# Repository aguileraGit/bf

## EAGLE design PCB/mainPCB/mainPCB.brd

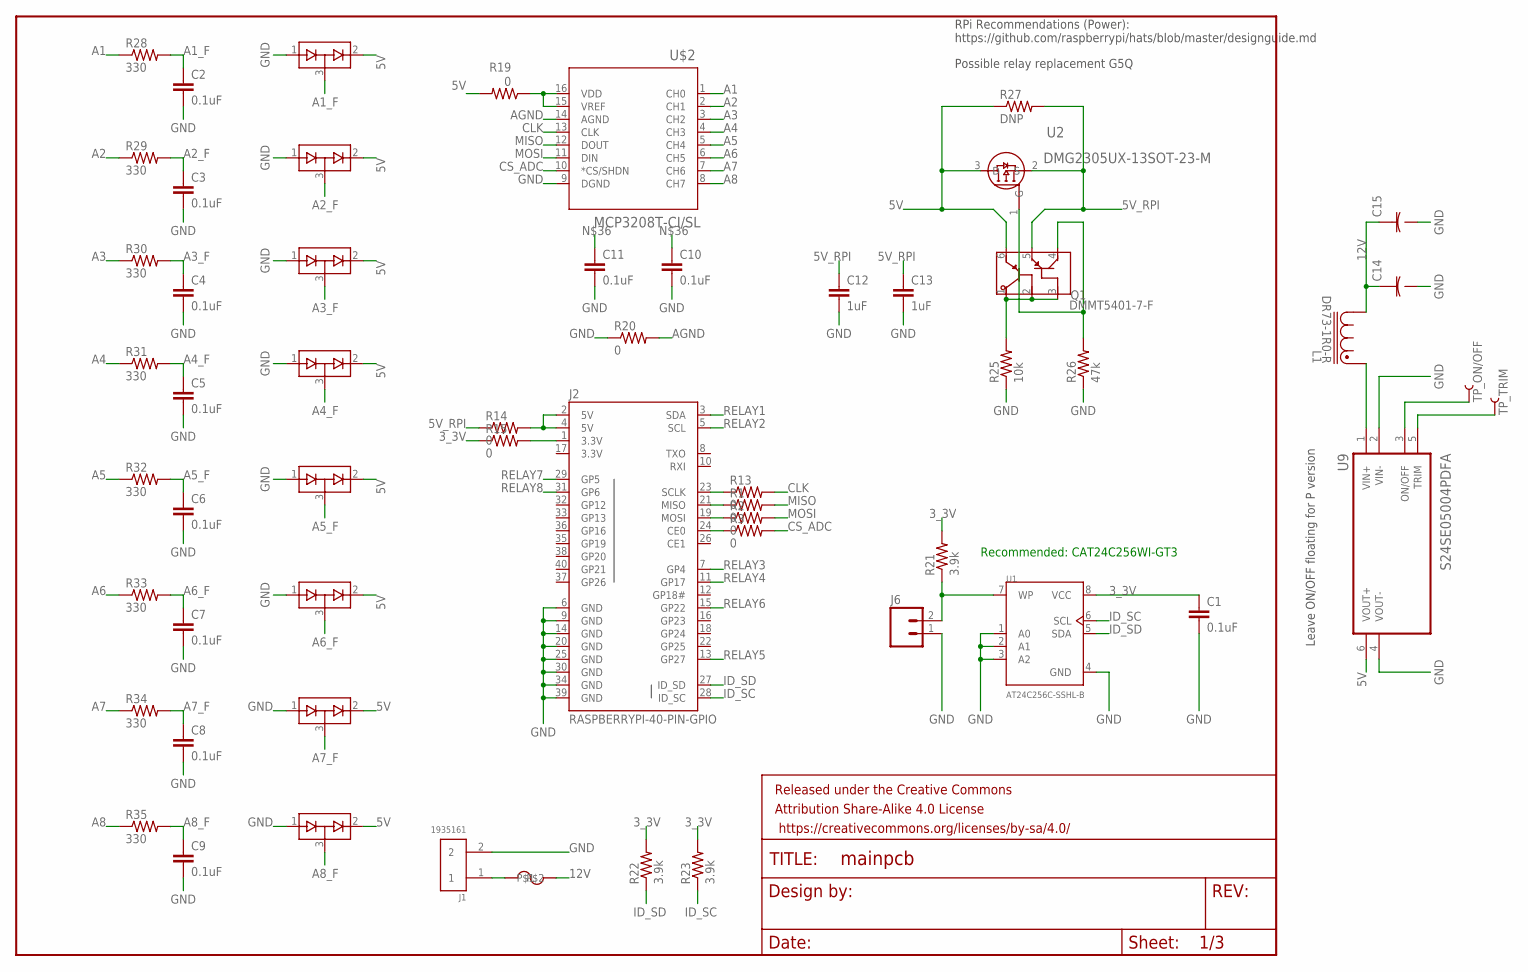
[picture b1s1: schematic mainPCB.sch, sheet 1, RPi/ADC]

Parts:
C1, C2, C3, C4, C5, C6, C7, C8, C9, C10, C11: 0.1uF; 0603-CAP
C12, C13: 1uF; 1206-CAP
C14, C15: EEE-HA1C471UPCAP_PAN_EEE_F-L; CAP_PAN_EEE_F-L
D1, D5, D7, D12, D13, D14, D15, D16: BAV99-7-F; SOT23-3
F9: 3544-2
FRAME2: FRAME-LETTERNO_PACKAGE; DUMMY
J1: 1935161; PHOENIX_1935161
J2: RASPBERRYPI-40-PIN-GPIO; 2X20-SHROUDED
J6: M02PTH; 1X02
L1: DR73-1R0-R; DR73
Q1: DMMT5401-7-F; SOT26
R1, R2, R3, R13, R19, R20: 0; 0603-RES
R14, R15: 0; 1206
R21, R22, R23: 3.9k; 0603-RES
R25: 10k; 0603-RES
R26: 47k; 0603-RES
R27: DNP; 1206
R28, R29, R30, R31, R32, R33, R34, R35: 330; 0603-RES
TP_ON/OFF: TEST-POINT3X5; PAD.03X.05
TP_TRIM: TEST-POINT3X5; PAD.03X.05
U1: AT24C256C-SSHL-B; SOIC127P600X175-8N
U2: DMG2305UX-13SOT-23-M; SOT-23-M
U9: S24SE05004PDFA; CONV_S24SE05002PDFA
U$2: MCP3208T-CI/SL; SOIC16-N_MC

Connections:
3.3V: J2.17 (3.3V)
3_3V: C1.1, R15.1, R21.2, R22.2, R23.2, U1.8 (VCC)
5V: D1.2 (C2), D5.2 (C2), D7.2 (C2), D12.2 (C2), D13.2 (C2), D14.2 (C2), D15.2 (C2), D16.2 (C2), Q1.6 (E1), R19.2, R27.1, U2.3 (D), U9.6 (VOUT+); also elsewhere on the board
5V_RPI: C12.1, C13.1, Q1.5 (E2), R14.1, R27.2, U2.2 (S)
12V: C14.1 (11), C15.1 (11), F9.P$3, F9.P$4, L1.2; also elsewhere on the board
A1: R28.1, U$2.1 (CH0)
A1_F: C2.1, D1.3 (COM), R28.2; also elsewhere on the board
A2: R29.1, U$2.2 (CH1)
A2_F: C3.1, D5.3 (COM), R29.2; also elsewhere on the board
A3: R30.1, U$2.3 (CH2)
A3_F: C4.1, D7.3 (COM), R30.2; also elsewhere on the board
A4: R31.1, U$2.4 (CH3)
A4_F: C5.1, D12.3 (COM), R31.2; also elsewhere on the board
A5: R32.1, U$2.5 (CH4)
A5_F: C6.1, D13.3 (COM), R32.2; also elsewhere on the board
A6: R33.1, U$2.6 (CH5)
A6_F: C7.1, D14.3 (COM), R33.2; also elsewhere on the board
A7: R34.1, U$2.7 (CH6)
A7_F: C8.1, D15.3 (COM), R34.2; also elsewhere on the board
A8: R35.1, U$2.8 (CH7)
A8_F: C9.1, D16.3 (COM), R35.2; also elsewhere on the board
AGND: R20.2, U$2.14 (AGND)
CLK: R13.2, U$2.13 (CLK)
CS_ADC: R3.2, U$2.10 (*CS/SHDN)
GND: C1.2, C2.2, C3.2, C4.2, C5.2, C6.2, C7.2, C8.2, C9.2, C10.2, C11.2, C12.2, C13.2, C14.2 (22), C15.2 (22), D1.1 (A1), D5.1 (A1), D7.1 (A1), D12.1 (A1), D13.1 (A1), D14.1 (A1), D15.1 (A1), D16.1 (A1), J1.2, J2.6 (GND), J2.9 (GND), J2.14 (GND), J2.20 (GND), J2.25 (GND), J2.30 (GND), J2.34 (GND), J2.39 (GND), J6.1, R20.1, R25.1, R26.1, U1.1 (A0), U1.2 (A1), U1.3 (A2), U1.4 (GND), U9.2 (VIN-), U9.4 (VOUT-), U$2.9 (DGND); also elsewhere on the board
ID_SC: J2.28 (ID_SC), R23.1, U1.6 (SCL)
ID_SD: J2.27 (ID_SD), R22.1, U1.5 (SDA)
MISO: R1.2, U$2.12 (DOUT)
MOSI: R2.2, U$2.11 (DIN)
unnamed: J2.2 (5V), J2.4 (5V), R14.2
unnamed: J2.1 (3.3V), R15.2
unnamed: J2.23 (SCLK), R13.1
unnamed: J2.21 (MISO), R1.1
unnamed: J2.19 (MOSI), R2.1
unnamed: J2.24 (CE0), R3.1
unnamed: Q1.1 (C1), Q1.2 (B1), Q1.3 (B2), R25.2
unnamed: Q1.4 (C2), R26.2, U2.1 (G)
unnamed: TP_ON/OFF.P$1, U9.3 (ON/OFF)
unnamed: C10.1, C11.1, R19.1, U$2.15 (VREF), U$2.16 (VDD)
unnamed: L1.1, U9.1 (VIN+)
unnamed: TP_TRIM.P$1, U9.5 (TRIM)
unnamed: F9.P$1, F9.P$2, J1.1
RELAY1: J2.3 (SDA); also elsewhere on the board
RELAY2: J2.5 (SCL); also elsewhere on the board
RELAY3: J2.7 (GP4); also elsewhere on the board
RELAY4: J2.11 (GP17); also elsewhere on the board
RELAY5: J2.13 (GP27); also elsewhere on the board
RELAY6: J2.15 (GP22); also elsewhere on the board
RELAY7: J2.29 (GP5); also elsewhere on the board
RELAY8: J2.31 (GP6); also elsewhere on the board
WP: J6.2, R21.1, U1.7 (WP)

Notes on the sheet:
Recommended: CAT24C256WI-GT3
RPi Recommendations (Power): https://github.com/raspberrypi/hats/blob/master/designguide.md
Possible relay replacement G5Q
Leave ON/OFF floating for P version

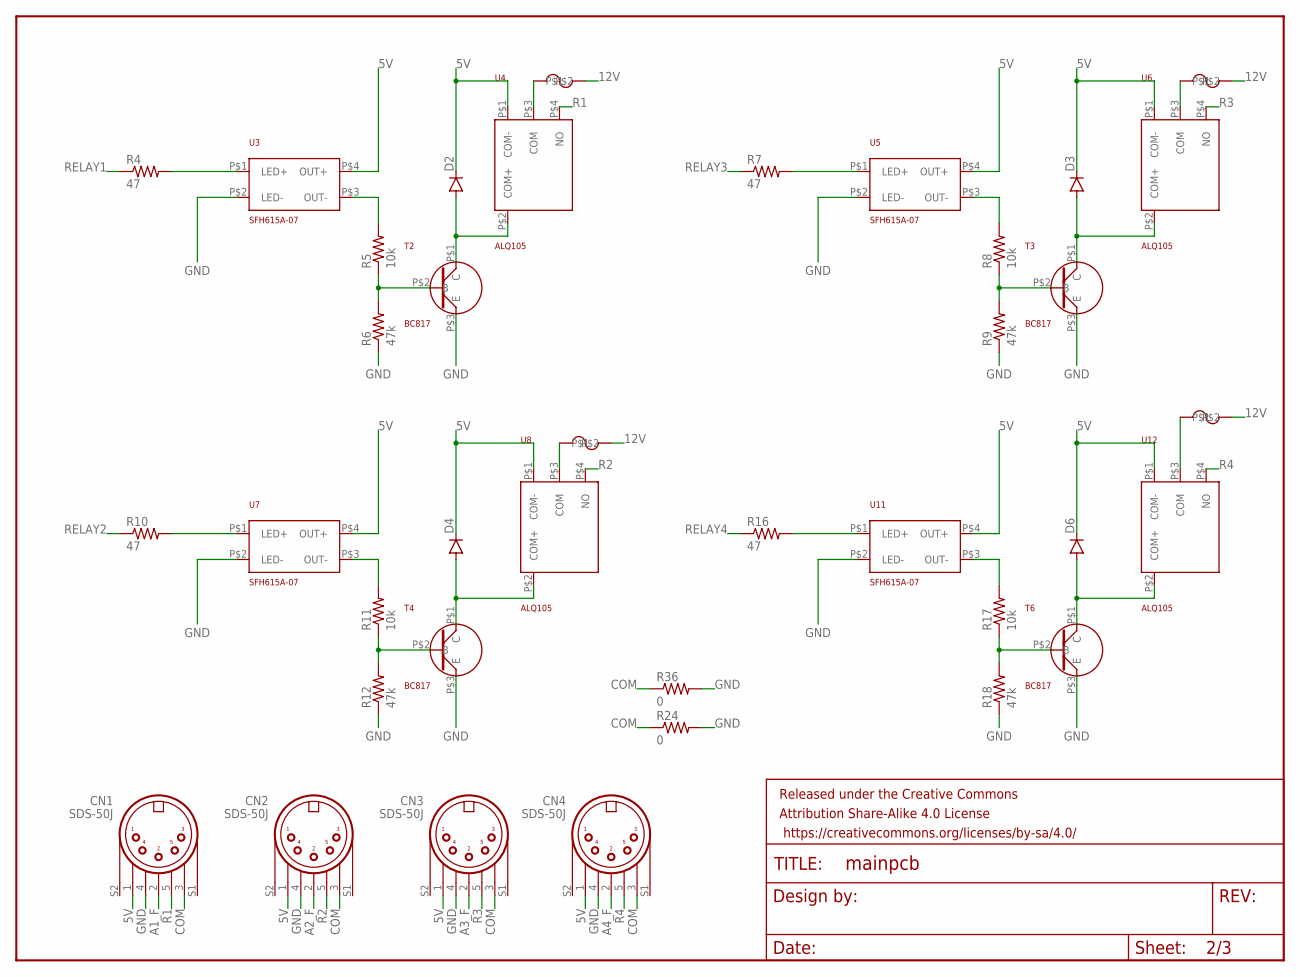
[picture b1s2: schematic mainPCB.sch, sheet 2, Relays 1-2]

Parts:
CN1, CN2, CN3, CN4: SDS-50J
D2, D3, D4, D6: DIODESMA; SMA-DIODE
F1, F2, F3, F4: 3544-2
FRAME1: FRAME-LETTERNO_PACKAGE; DUMMY
R4, R7, R10, R16: 47; 0603-RES
R5, R8, R11, R17: 10k; 0603-RES
R6, R9, R12, R18: 47k; 0603-RES
R24, R36: 0; 1206
T2, T3, T4, T6: BC817
U3, U5, U7, U11: SFH615A-07
U4, U6, U8, U12: ALQ105

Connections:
5V: CN1.1, CN2.1, CN3.1, CN4.1, D2.C, D3.C, D4.C, D6.C, U3.P$4 (OUT+), U4.P$1 (COM-), U5.P$4 (OUT+), U6.P$1 (COM-), U7.P$4 (OUT+), U8.P$1 (COM-), U11.P$4 (OUT+), U12.P$1 (COM-); also elsewhere on the board
12V: F1.P$3, F1.P$4, F2.P$3, F2.P$4, F3.P$3, F3.P$4, F4.P$3, F4.P$4; also elsewhere on the board
A1_F: CN1.2; also elsewhere on the board
A2_F: CN2.2; also elsewhere on the board
A3_F: CN3.2; also elsewhere on the board
A4_F: CN4.2; also elsewhere on the board
COM: CN1.3, CN2.3, CN3.3, CN4.3, R24.1, R36.1; also elsewhere on the board
GND: CN1.4, CN2.4, CN3.4, CN4.4, R6.1, R9.1, R12.1, R18.1, R24.2, R36.2, T2.P$3 (E), T3.P$3 (E), T4.P$3 (E), T6.P$3 (E), U3.P$2 (LED-), U5.P$2 (LED-), U7.P$2 (LED-), U11.P$2 (LED-); also elsewhere on the board
unnamed: F1.P$1, F1.P$2, U4.P$3 (COM)
unnamed: F2.P$1, F2.P$2, U8.P$3 (COM)
unnamed: F4.P$1, F4.P$2, U12.P$3 (COM)
unnamed: F3.P$1, F3.P$2, U6.P$3 (COM)
unnamed: R4.2, U3.P$1 (LED+)
unnamed: R5.2, U3.P$3 (OUT-)
unnamed: R5.1, R6.2, T2.P$2 (B)
unnamed: D2.A, T2.P$1 (C), U4.P$2 (COM+)
unnamed: R7.2, U5.P$1 (LED+)
unnamed: R8.2, U5.P$3 (OUT-)
unnamed: R8.1, R9.2, T3.P$2 (B)
unnamed: D3.A, T3.P$1 (C), U6.P$2 (COM+)
unnamed: R10.2, U7.P$1 (LED+)
unnamed: R11.2, U7.P$3 (OUT-)
unnamed: R11.1, R12.2, T4.P$2 (B)
unnamed: D4.A, T4.P$1 (C), U8.P$2 (COM+)
unnamed: R16.2, U11.P$1 (LED+)
unnamed: R17.2, U11.P$3 (OUT-)
unnamed: R17.1, R18.2, T6.P$2 (B)
unnamed: D6.A, T6.P$1 (C), U12.P$2 (COM+)
R1: CN1.5, U4.P$4 (NO)
R2: CN2.5, U8.P$4 (NO)
R3: CN3.5, U6.P$4 (NO)
R4: CN4.5, U12.P$4 (NO)
RELAY1: R4.1; also elsewhere on the board
RELAY2: R10.1; also elsewhere on the board
RELAY3: R7.1; also elsewhere on the board
RELAY4: R16.1; also elsewhere on the board

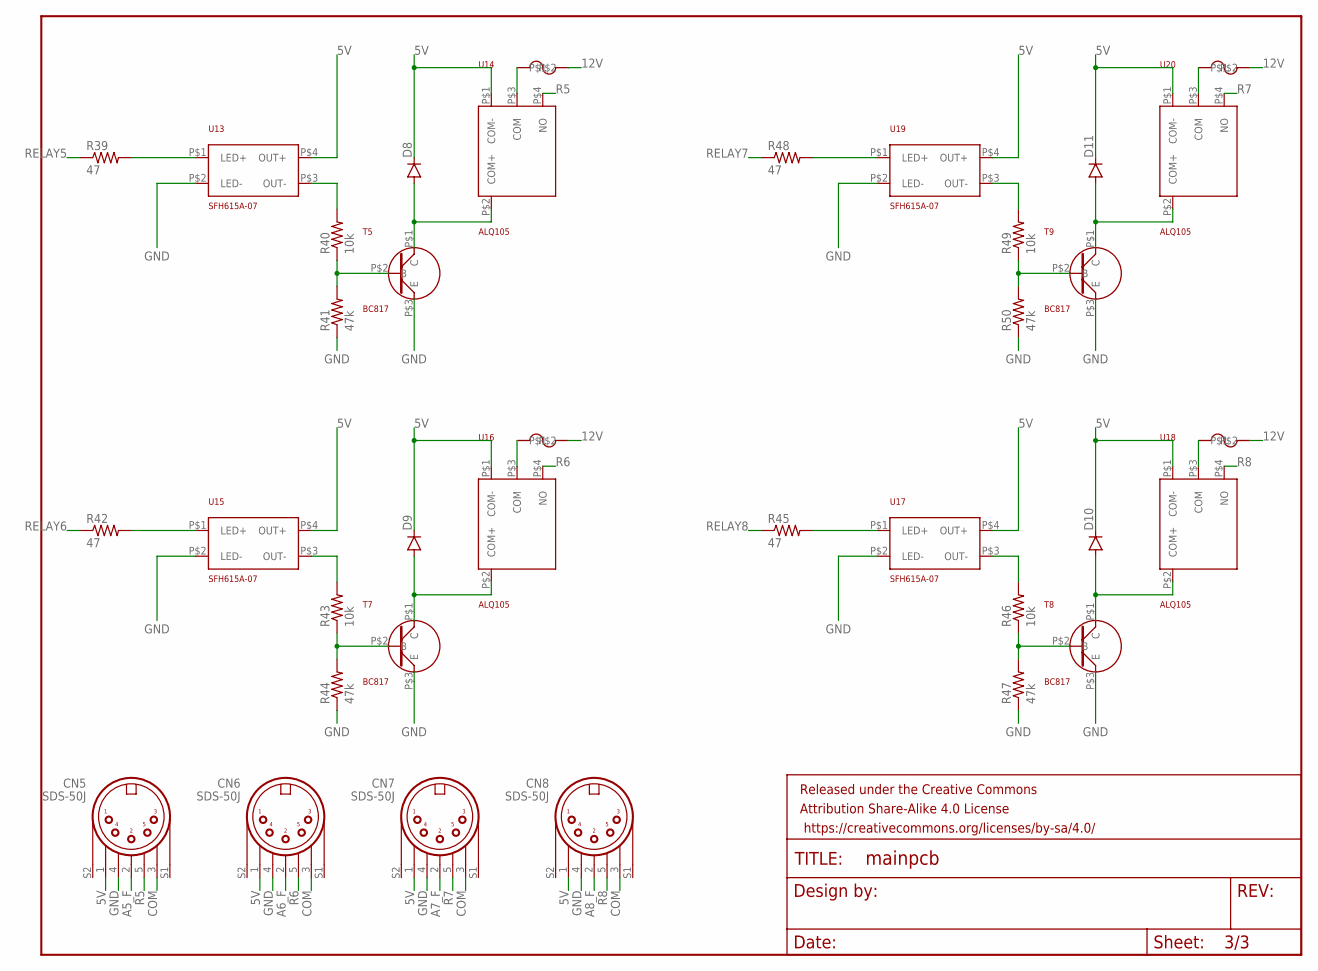
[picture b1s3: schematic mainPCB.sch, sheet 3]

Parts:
CN5, CN6, CN7, CN8: SDS-50J
D8, D9, D10, D11: DIODESMA; SMA-DIODE
F5, F6, F7, F8: 3544-2
FRAME3: FRAME-LETTER; CREATIVE_COMMONS
R39, R42, R45, R48: 47; 0603-RES
R40, R43, R46, R49: 10k; 0603-RES
R41, R44, R47, R50: 47k; 0603-RES
T5, T7, T8, T9: BC817
U13, U15, U17, U19: SFH615A-07
U14, U16, U18, U20: ALQ105

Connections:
5V: CN5.1, CN6.1, CN7.1, CN8.1, D8.C, D9.C, D10.C, D11.C, U13.P$4 (OUT+), U14.P$1 (COM-), U15.P$4 (OUT+), U16.P$1 (COM-), U17.P$4 (OUT+), U18.P$1 (COM-), U19.P$4 (OUT+), U20.P$1 (COM-); also elsewhere on the board
12V: F5.P$3, F5.P$4, F6.P$3, F6.P$4, F7.P$3, F7.P$4, F8.P$3, F8.P$4; also elsewhere on the board
A5_F: CN5.2; also elsewhere on the board
A6_F: CN6.2; also elsewhere on the board
A7_F: CN7.2; also elsewhere on the board
A8_F: CN8.2; also elsewhere on the board
COM: CN5.3, CN6.3, CN7.3, CN8.3; also elsewhere on the board
GND: CN5.4, CN6.4, CN7.4, CN8.4, R41.1, R44.1, R47.1, R50.1, T5.P$3 (E), T7.P$3 (E), T8.P$3 (E), T9.P$3 (E), U13.P$2 (LED-), U15.P$2 (LED-), U17.P$2 (LED-), U19.P$2 (LED-); also elsewhere on the board
unnamed: F5.P$1, F5.P$2, U14.P$3 (COM)
unnamed: F6.P$1, F6.P$2, U16.P$3 (COM)
unnamed: F7.P$1, F7.P$2, U20.P$3 (COM)
unnamed: F8.P$1, F8.P$2, U18.P$3 (COM)
unnamed: R39.2, U13.P$1 (LED+)
unnamed: R40.2, U13.P$3 (OUT-)
unnamed: R40.1, R41.2, T5.P$2 (B)
unnamed: D8.A, T5.P$1 (C), U14.P$2 (COM+)
unnamed: R42.2, U15.P$1 (LED+)
unnamed: R43.2, U15.P$3 (OUT-)
unnamed: R43.1, R44.2, T7.P$2 (B)
unnamed: D9.A, T7.P$1 (C), U16.P$2 (COM+)
unnamed: R45.2, U17.P$1 (LED+)
unnamed: R46.2, U17.P$3 (OUT-)
unnamed: R46.1, R47.2, T8.P$2 (B)
unnamed: D10.A, T8.P$1 (C), U18.P$2 (COM+)
unnamed: R48.2, U19.P$1 (LED+)
unnamed: R49.2, U19.P$3 (OUT-)
unnamed: R49.1, R50.2, T9.P$2 (B)
unnamed: D11.A, T9.P$1 (C), U20.P$2 (COM+)
R5: CN5.5, U14.P$4 (NO)
R6: CN6.5, U16.P$4 (NO)
R7: CN7.5, U20.P$4 (NO)
R8: CN8.5, U18.P$4 (NO)
RELAY5: R39.1; also elsewhere on the board
RELAY6: R42.1; also elsewhere on the board
RELAY7: R48.1; also elsewhere on the board
RELAY8: R45.1; also elsewhere on the board

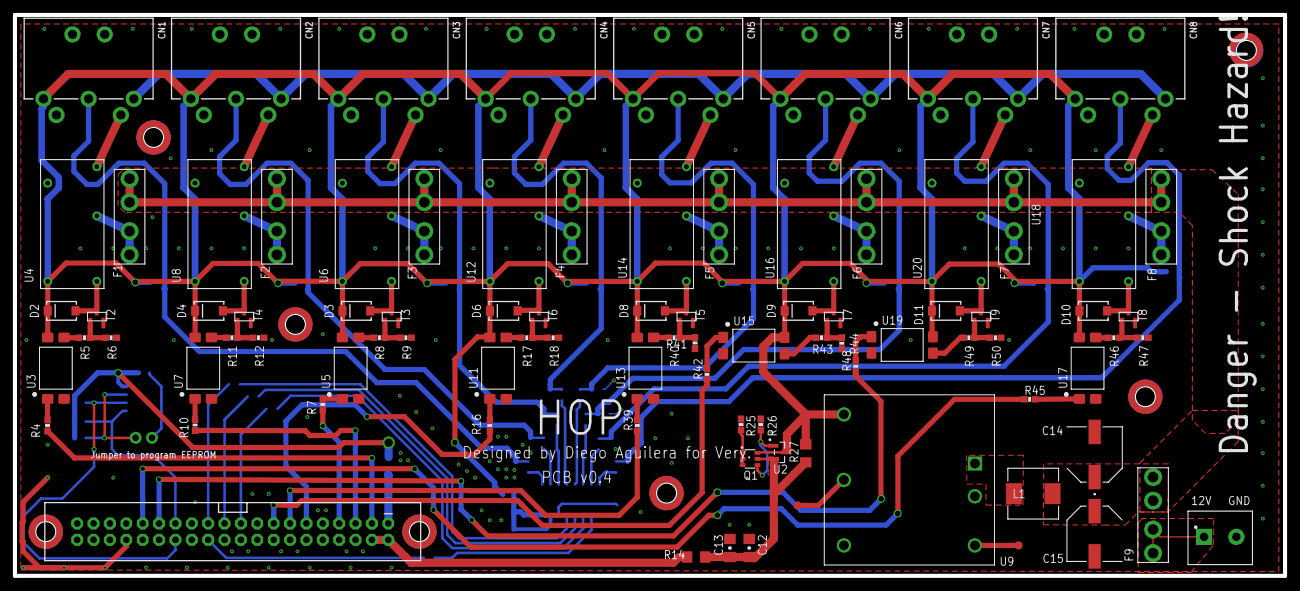
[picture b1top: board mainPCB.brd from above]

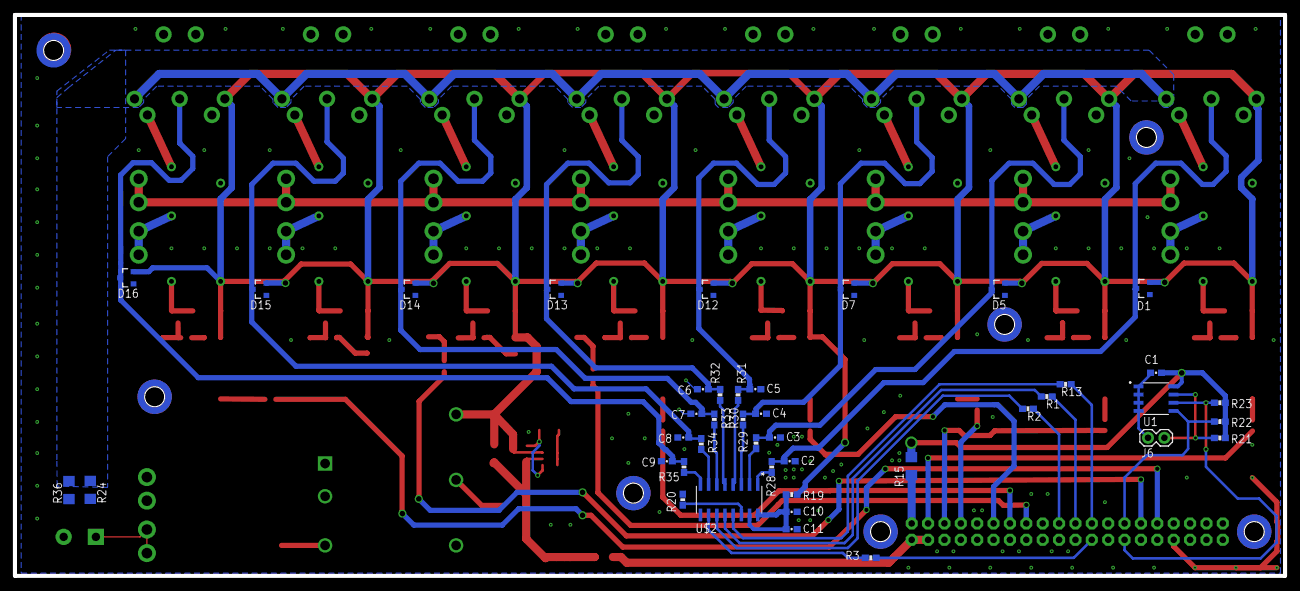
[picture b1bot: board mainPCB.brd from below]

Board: 2 copper layers, 197.0 x 87.0 mm, 134 parts (42 on the bottom side), 99 nets.

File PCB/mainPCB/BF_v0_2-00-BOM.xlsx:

Populate | Qty | Value | Device | Package | Parts | Manufacture PN | DigiKey PN | 1 |  | 10 |  | 100 |  | Description | AVAILABILITY | DESCRIPTION | DESIGNER | DIGI-KEY_PART_NUMBER | DIGI-KEY_PURCHASE_URL | MANUFACTURER_PART_NUMBER | MF | MP | PACKAGE | PRICE | PROD_ID | VALUE | VENDOR | VERSION
Y | 9 |  | DIODESMA | SMA-DIODE | D2, D3, D4, D5, D6, D8, D9, D10, D11 | CDBA5200-HF | 641-1706-1-ND | 0.59 | 5.31 | 0.49299999999999999 | 44.37 | 0.36990000000000001 | 332.91 | Diode
Y | 1 |  | M02PTH | 1X02 | J6 | M20-9990246 | 952-2262-ND | 0.11 | 0.11 | 9.9000000000000005E-2 | 0.99 | 6.0900000000000003E-2 | 6.09 | Standard 2-pin 0.1 header. Use with"
Y | 6 | 0 | RESISTOR0603-RES | 0603-RES | R1, R2, R3, R13, R19, R20 | RC0603JR-070RL | 311-0.0GRCT-ND | 0.1 | 0.60000000000000009 | 0.01 | 0.6 | 4.1000000000000003E-3 | 2.4600000000000004 | Resistor
Y | 3 | 0 | RESISTOR1206 | 1206 | R14, R15, R24 | RC1206JR-070RL | 311-0.0ERCT-ND | 0.1 | 0.30000000000000004 | 2.4E-2 | 0.72 | 9.7000000000000003E-3 | 2.91 | Resistor
Y | 11 | 0.1uF | 0.1UF-25V(+80/-20%)(0603) | 0603-CAP | C1, C2, C3, C4, C5, C6, C7, C8, C9, C10, C11 | GRM188R70J104KA01D | 490-9730-1-ND | 0.1 | 1.1000000000000001 | 7.0999999999999994E-2 | 7.81 | 3.1600000000000003E-2 | 34.760000000000005 | CAP-00810 |  |  |  |  |  |  |  |  |  |  | CAP-00810 | 0.1uF
Y | 2 | 10uF | 1.0UF50V10%(1206) | 1206-CAP | C12, C13 | LMK316B7106KL-TD | 587-2596-1-ND | 0.27 | 0.54 | 0.182 | 3.6399999999999997 | 0.1032 | 20.64 | CAP-09822 |  |  |  |  |  |  |  |  |  |  | CAP-09822 | 1.0uF
Y | 9 | 10k | RESISTOR0603-RES | 0603-RES | R5, R8, R11, R17, R25, R40, R43, R46, R49 | RC0603FR-0710KL | 311-10.0KHRCT-ND | 0.1 | 0.9 | 1.4999999999999999E-2 | 1.3499999999999999 | 6.0000000000000001E-3 | 5.4 | Resistor
Y | 1 | 1776244-4 | 1776244-4 | 1776244-4 | CON1 | 1776244-4 | A97998-ND | 1.74 | 1.74 | 1.2250000000000001 | 12.25 | 1.0319 | 103.19 | TE 1776244-4
Y | 3 | 3.9k | RESISTOR0603-RES | 0603-RES | R21, R22, R23 | RC0603FR-073K9L | 311-3.90KHRDKR-ND | 0.1 | 0.30000000000000004 | 1.4999999999999999E-2 | 0.44999999999999996 | 6.0000000000000001E-3 | 1.8 | Resistor
Y | 8 | 330 | RESISTOR0603-RES | 0603-RES | R28, R29, R30, R31, R32, R33, R34, R35 | RC0603FR-07300RL | 311-300HRCT-ND | 0.1 | 0.8 | 1.4999999999999999E-2 | 1.2 | 6.0000000000000001E-3 | 4.8 | Resistor
Y | 8 | 3544-2 | 3544-2 | 3544-2 | F1, F2, F3, F4, F5, F6, F7, F8 | 3544-2 | 36-3544-2-ND | 0.91 | 7.28 | 0.77800000000000002 | 62.24 | 0.6714 | 537.12 | Keystone Electronics Fuse Holder - 3544-2
Y | 8 | 47 | RESISTOR0603-RES | 0603-RES | R4, R7, R10, R16, R39, R42, R45, R48 | RC0603FR-0747RL | 311-47.0HRCT-ND | 0.1 | 0.8 | 1.4999999999999999E-2 | 1.2 | 6.0000000000000001E-3 | 4.8 | Resistor
Y | 9 | 47k | RESISTOR0603-RES | 0603-RES | R6, R9, R12, R18, R26, R41, R44, R47, R50 | RC0603FR-0747KL | 311-47.0KHRCT-ND | 0.1 | 0.9 | 1.4999999999999999E-2 | 1.3499999999999999 | 6.0000000000000001E-3 | 5.4 | Resistor
Y | 8 | ALQ105 | ALQ105 | ALQ105 | U4, U6, U8, U12, U14, U16, U18, U20 | ALQ105 | 255-3565-ND | 2.42 | 19.36 | 2.2730000000000001 | 181.84 | 1.8180000000000001 | 1454.4 | ALQ105 Solenoid
Y | 1 | AT24C256C-SSHL-B | AT24C256C-SSHL-B | SOIC127P600X175-8N | U1 | AT24C256C-SSHL-B | AT24C256C-SSHL-B-ND | 0.69 | 0.69 | 0.63100000000000001 | 6.3100000000000005 | 0.55369999999999997 | 55.37 | EEPROM Serial-2Wire 256K-bit 32K x 8 1.8V/2.5V/3.3V/5V 8-Pin SOIC Bulk |  | EEPROM Serial-2Wire 256K-bit 32K x 8 1.8V/2.5V/3.3V/5V 8-Pin SOIC Bulk |  | AT24C256C-SSHL-B-ND | https://www.digikey.com/product-detail/en/microchip-technolo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 |  | Atmel | AT24C256C-SSHL-B | SOIC-8 Atmel
Y | 8 | BC817 | BC817 | BC817 | T2, T3, T4, T5, T6, T7, T8, T9 | BC817-25-7-F | BC817-25FDICT-ND | 0.22 | 1.76 | 0.183 | 14.64 | 9.69E-2 | 77.52 | NPN Transistor BC817
Y | 1 | DMG2305UX-13SOT-23-M | DMG2305UX-13SOT-23-M | SOT-23-M | U2 | DMG2305UX-13 | DMG2305UX-13DICT-ND | 0.44 | 0.44 | 0.39800000000000002 | 3.9800000000000004 | 0.2228 | 22.28 |  |  |  |  |  |  | DMG2305UX13 |  |  |  |  |  |  | Diodes Inc
Y | 1 | DMMT5401-7-F | DMMT5401-7-F | SOT26 | Q1 | DMMT5401-7-F | DMMT5401-FDICT-ND | 0.46 | 0.46 | 0.34599999999999997 | 3.46 | 0.21529999999999999 | 21.529999999999998 | http://octopart.com/dmmt5401-7-f-diodes+inc.-39560120 |  | DMMT5401 Series PNP 150 V 300 mW Small Signal Transistor SMT - SOT-26-6 |  | DMMT5401-FDICT-ND | https://www.digikey.com/product-detail/en/diodes-incorporate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 |  | Diodes Inc. | DMMT5401-7-F | SOT-23 Diodes Inc.
N | 1 | DNP | RESISTOR1206 | 1206 | R27 |  |  |  |  |  |  |  |  | Resistor
Y | 2 | EEE-HA1C471UPCAP_PAN_EEE_F-L | EEE-HA1C471UPCAP_PAN_EEE_F-L | CAP_PAN_EEE_F-L | C14, C15 | EEE-HA1C471UP | PCE4192CT-ND | 0.68 | 1.36 | 0.48099999999999998 | 9.6199999999999992 | 0.31659999999999999 | 63.32 |  |  |  |  |  |  | EEEHA1C471UP |  |  |  |  |  |  | PANASONIC
N | 1 | FRAME-LETTER | FRAME-LETTER | CREATIVE_COMMONS | FRAME3 |  |  |  |  |  |  |  |  | Schematic Frame
N | 2 | FRAME-LETTERNO_PACKAGE | FRAME-LETTERNO_PACKAGE | DUMMY | FRAME1, FRAME2 |  |  |  |  |  |  |  |  | Schematic Frame |  |  | Nobody |  |  |  |  |  |  |  |  |  |  | v01
Y | 1 | MCP3208T-CI/SL | MCP3208T-CI/SL | SOIC16-N_MC | U$2 | MCP3208T-CI/SL | MCP3208T-CI/SLCT-ND | 3.65 | 3.65 | 3.65 | 36.5 | 2.7719999999999998 | 277.2 | Microchip MCP3208 ADC | Good | 8 Channel SPI Serial Interface 2.7 V 12-Bit A/D Converter SMT - SOIC-16 |  |  |  |  | Microchip | MCP3208T-CI/SL | SOIC-16 Microchip | 3.04 USD
N | 1 | RASPBERRYPI-40-PIN-GPIO | RASPBERRYPI-40-PIN-GPIO | 2X20-SHROUDED | J2 |  |  |  |  |  |  |  |  | Second Generation Raspberry Pi GPIO Header
Y | 8 | SDS-50J | SDS-50J | SDS-50J | CN1, CN2, CN3, CN4, CN5, CN6, CN7, CN8 | SDS-50J | CP-2350-ND | 1.17 | 9.36 | 1.028 | 82.240000000000009 | 0.88660000000000005 | 709.28000000000009 | DIN 5-Pin - Circular | Good | 5 Pin%2C Right-Angle Receptacle%2C 180%C2%B0 |  |  |  |  | CUI | SDS-50J | None | 0.77 USD
Y | 8 | SFH615A-07 | SFH615A-07 | SFH615A-07 | U3, U5, U7, U11, U13, U15, U17, U19 | SFH615A-4X017T | SFH615A-4X017TCT-ND | 1.03 | 8.24 | 0.84 | 67.2 | 0.58160000000000001 | 465.28000000000003 | Vishay Optocoupler SFH615A-007
N | 1 |  | Fuse |  |  | 0287002.PXCN | F4192-ND | 0.28000000000000003 | 0.28000000000000003 | 0.26 | 2.6 | 0.216 | 21.6
 |  |  |  |  |  |  | Total Cost |  | 66.279999999999987 |  | 546.56000000000006 |  | 4230.0600000000013
 |  |  |  |  |  |  | Cost per board |  | 66.279999999999987 |  | 54.656000000000006 |  | 42.30060000000001

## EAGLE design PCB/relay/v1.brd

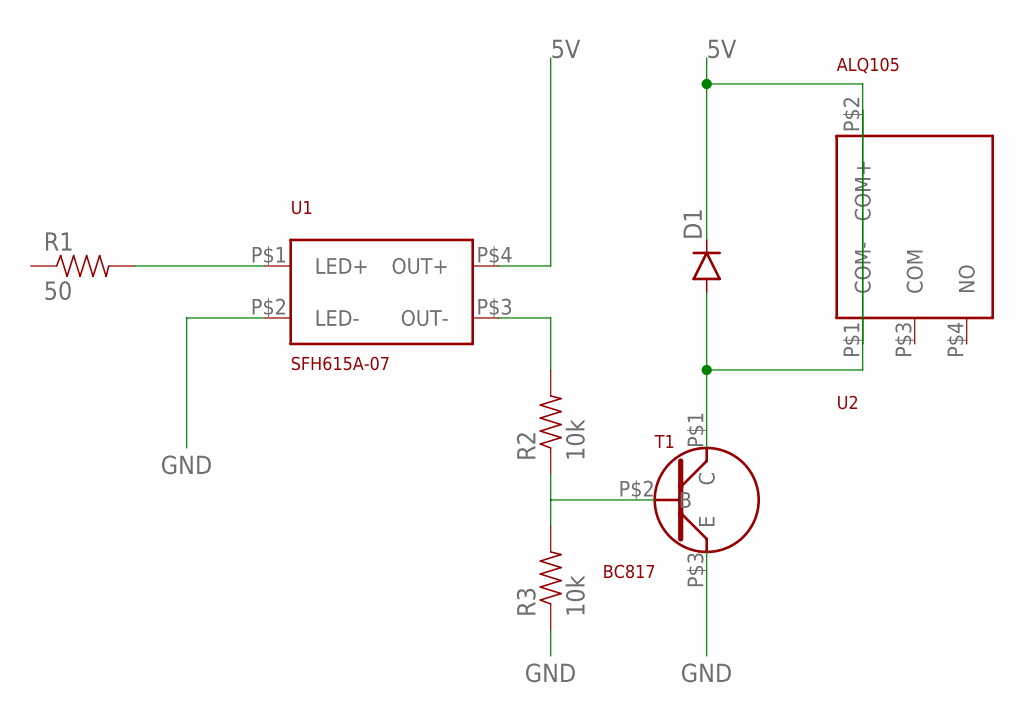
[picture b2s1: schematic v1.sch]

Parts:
D1: DIODESMA; SMA-DIODE
R1: 50; 0603-RES
R2, R3: 10k; 0603-RES
T1: BC817
U1: SFH615A-07
U2: ALQ105

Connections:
5V: D1.C, U1.P$4 (OUT+), U2.P$1 (COM-)
GND: R3.1, T1.P$3 (E), U1.P$2 (LED-)
unnamed: R1.2, U1.P$1 (LED+)
unnamed: R2.2, U1.P$3 (OUT-)
unnamed: R2.1, R3.2, T1.P$2 (B)
unnamed: D1.A, T1.P$1 (C), U2.P$2 (COM+)

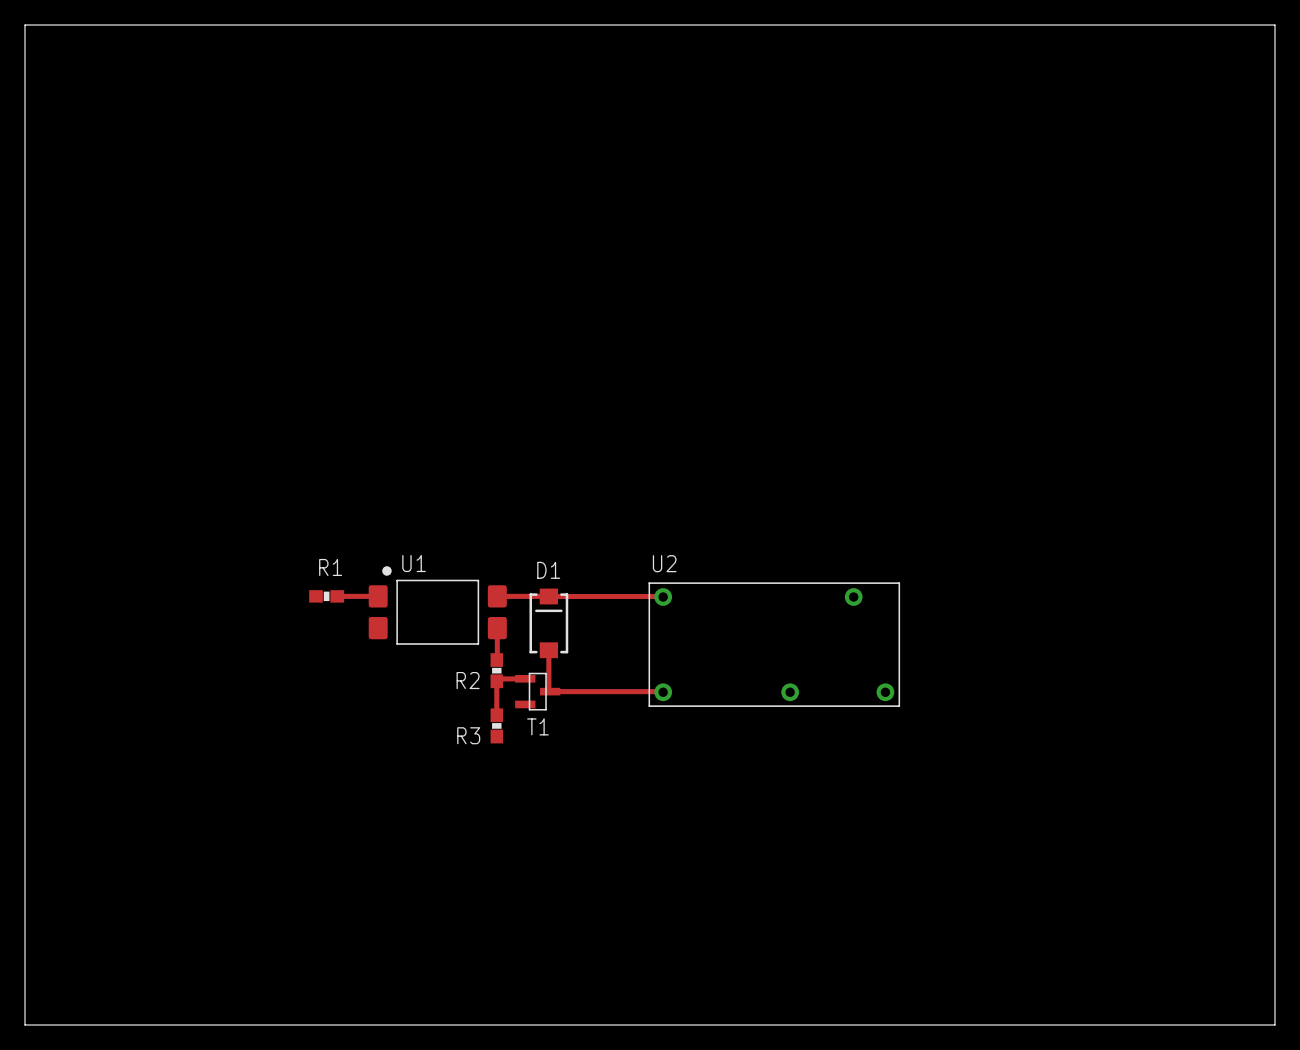
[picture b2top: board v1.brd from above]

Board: 2 copper layers, 100.0 x 80.0 mm, 7 parts (0 on the bottom side), 6 nets.

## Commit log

2017-10-07 Version 1 Ordered.
2017-12-04 Adding files for v0.2
2017-12-10 Removed Diode.
2018-01-02 Adding files
2018-02-24 Technically version 0.4. Sending it to JLCPCB for production.
2018-03-08 Added all design files for v0.4. Cleaned up old files.
2018-03-08 Adding Design Files for v0.4

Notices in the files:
parts and their libraries:
SparkFun-DiscreteSemi: Licensing: Creative Commons ShareAlike 4.0 International - https://creativecommons.org/licenses/by-sa/4.0
SparkFun-Aesthetics: Released under the Creative Commons
SparkFun-Aesthetics: https://creativecommons.org/licenses/by-sa/4.0
